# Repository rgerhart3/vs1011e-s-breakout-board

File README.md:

# vs1011e-s-breakout-board
KiCad files for the vs1011E-S breakout board (ECE 4180)

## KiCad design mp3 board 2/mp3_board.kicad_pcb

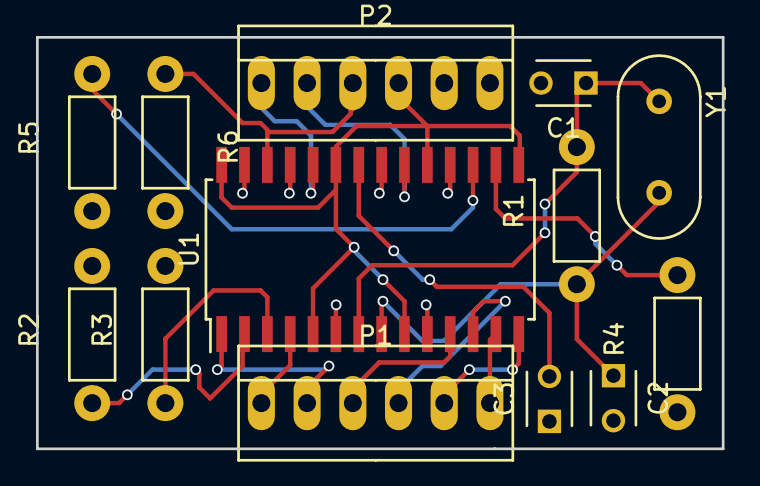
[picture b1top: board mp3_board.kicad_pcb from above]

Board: 2 copper layers, 38.1 x 22.9 mm, 13 parts (0 on the bottom side), 18 nets.

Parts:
C1, C2: 33p; C_Disc_D3_P2.5
C3: 100nF; C_Disc_D3_P2.5
P1, P2: CONN_01X06; PINHEAD1-6
R1: 1M; Resistor_Horizontal_RM7mm
R2, R3, R4, R5, R6: 100K; Resistor_Horizontal_RM7mm
U1: VS1011E-S; SOIC-28W_7.5x17.9mm_Pitch1.27mm
Y1: Crystal; HC-49V

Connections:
GND: C1.2, C2.2, C3.1, P2.5, R2.2, R3.2, R4.1, R5.1, R6.2, U1.6, U1.10, U1.18, U1.21, U1.25, U1.27
unnamed: C1.1, R1.2, U1.7, Y1.1
unnamed: C2.1, R1.1, U1.8, Y1.2
unnamed: C3.2, U1.22
unnamed: P1.1, U1.4
unnamed: P1.2, U1.1
unnamed: P1.3, U1.11
unnamed: P1.4, U1.12
unnamed: P1.5, U1.14
unnamed: P1.6, U1.13
unnamed: P2.1, U1.24
unnamed: P2.2, U1.20
unnamed: P2.3, R6.1, U1.26
unnamed: R2.1, U1.2
unnamed: R3.1, U1.3
unnamed: R4.2, U1.16
unnamed: R5.2, U1.17
VCC: P2.4, U1.5, U1.9, U1.15, U1.19, U1.23, U1.28
